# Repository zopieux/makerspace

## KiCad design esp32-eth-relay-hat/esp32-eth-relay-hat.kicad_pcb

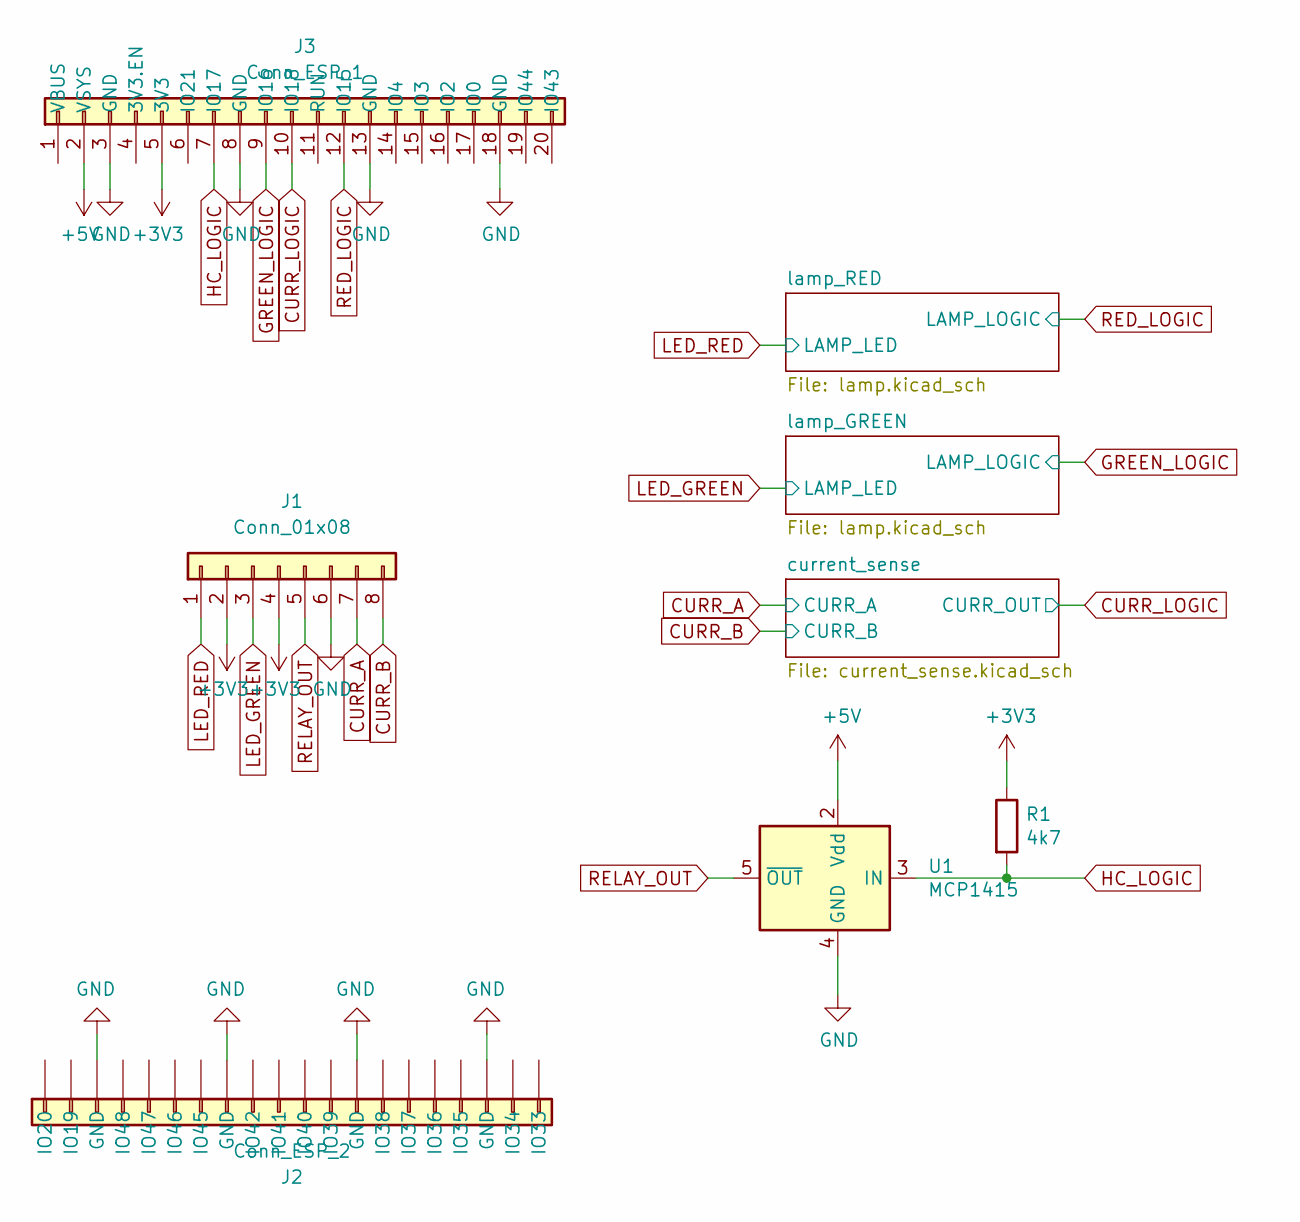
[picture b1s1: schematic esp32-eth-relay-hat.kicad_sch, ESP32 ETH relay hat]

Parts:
J1: Conn_01x08; TerminalBlock_Phoenix_MKDS-1,5-8_1x08_P5.00mm_Horizontal
J2: Conn_ESP_2; PinSocket_1x20_P2.54mm_Vertical
J3: Conn_ESP_1; PinSocket_1x20_P2.54mm_Vertical
R1: 4k7; R_0603_1608Metric_Pad0.98x0.95mm_HandSolder
U1: MCP1415; SOT-23-5

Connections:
+3V3: J1.2, J1.4, J3.5 (3V3), R1.1
+5V: J3.2 (VSYS), U1.2 (Vdd); also elsewhere on the board
CURR_A: J1.7; also elsewhere on the board
CURR_B: J1.8; also elsewhere on the board
CURR_LOGIC: J3.10 (IO18); also elsewhere on the board
GND: J1.6, J2.3 (GND), J2.8 (GND), J2.13 (GND), J2.18 (GND), J3.3 (GND), J3.8 (GND), J3.13 (GND), J3.18 (GND), U1.4 (GND); also elsewhere on the board
GREEN_LOGIC: J3.9 (IO16); also elsewhere on the board
HC_LOGIC: J3.7 (IO17), R1.2, U1.3 (IN)
LED_GREEN: J1.3; also elsewhere on the board
LED_RED: J1.1; also elsewhere on the board
RED_LOGIC: J3.12 (IO15); also elsewhere on the board
RELAY_OUT: J1.5, U1.5 (~OUT)

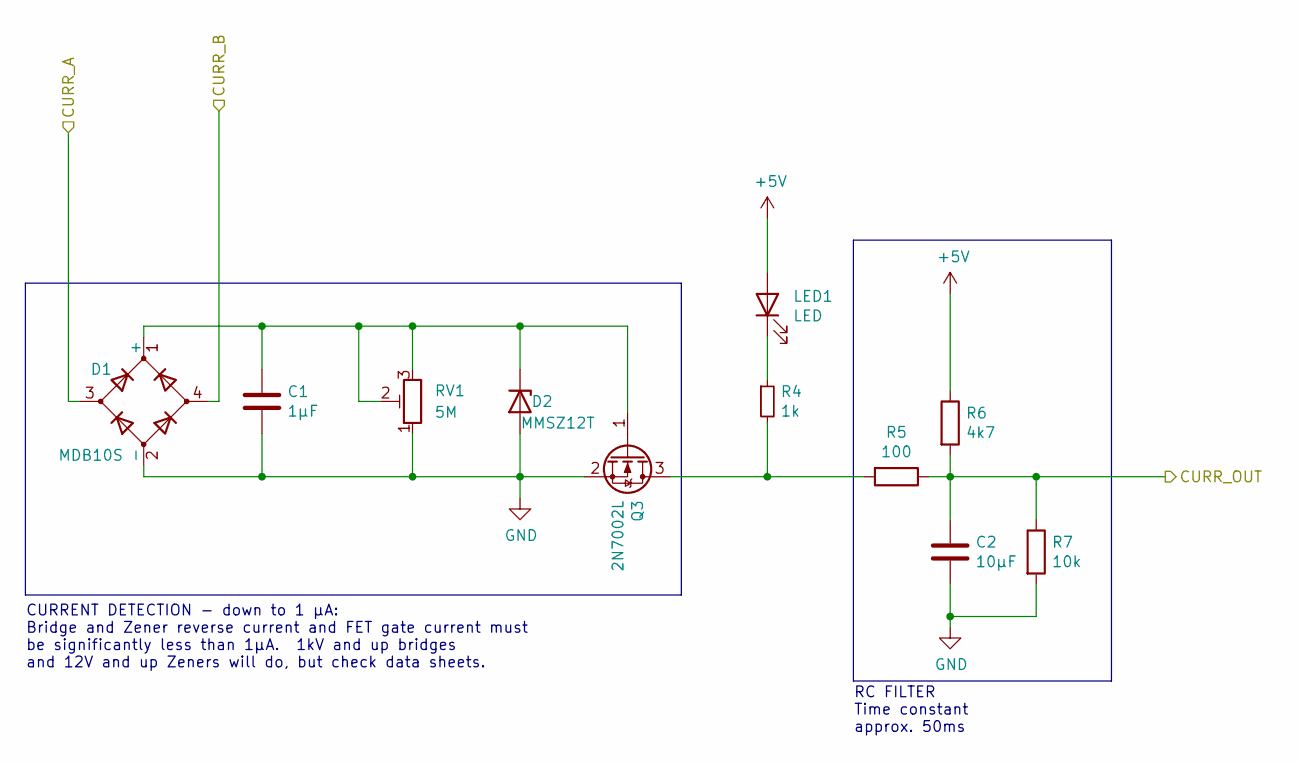
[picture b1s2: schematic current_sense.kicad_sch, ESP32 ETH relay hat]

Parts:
C1: 1µF; C_0603_1608Metric_Pad1.08x0.95mm_HandSolder
C2: 10µF; C_0603_1608Metric_Pad1.08x0.95mm_HandSolder
D1: MDB10S; Diode_Bridge_Diotec_ABS
D2: MMSZ12T; D_SOD-123
LED1: LED; LED_0603_1608Metric_Pad1.05x0.95mm_HandSolder
Q3: 2N7002L; SOT-23_Handsoldering
R4: 1k; R_0603_1608Metric_Pad0.98x0.95mm_HandSolder
R5: 100; R_0603_1608Metric_Pad0.98x0.95mm_HandSolder
R6: 4k7; R_0603_1608Metric_Pad0.98x0.95mm_HandSolder
R7: 10k; R_0603_1608Metric_Pad0.98x0.95mm_HandSolder
RV1: 5M; Potentiometer_Bourns_3386P_Vertical

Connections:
+5V: LED1.2 (A), R6.1; also elsewhere on the board
CURR_A: D1.3; also elsewhere on the board
CURR_B: D1.4; also elsewhere on the board
CURR_LOGIC: C2.1, R5.1, R6.2, R7.1; also elsewhere on the board
GND: C1.2, C2.2, D1.2 (-), D2.2 (A), Q3.2 (S), R7.2, RV1.1; also elsewhere on the board
unnamed: C1.1, D1.1 (+), D2.1 (K), Q3.1 (G), RV1.2, RV1.3
unnamed: LED1.1 (K), R4.1
unnamed: Q3.3 (D), R4.2, R5.2

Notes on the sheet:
RC FILTER Time constant approx. 50ms
CURRENT DETECTION - down to 1 µA: Bridge and Zener reverse current and FET gate current must be significantly less than 1µA. 1kV and up bridges and 12V and up Zeners will do, but check data sheets.

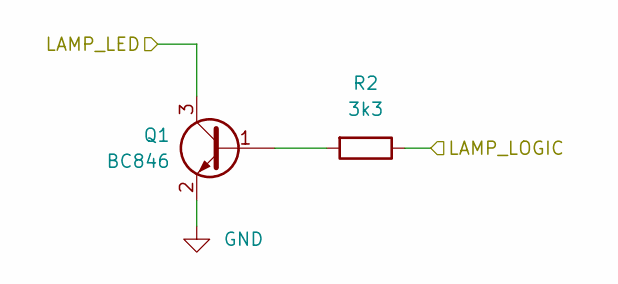
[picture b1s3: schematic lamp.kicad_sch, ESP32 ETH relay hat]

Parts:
Q1: BC846; SOT-23_Handsoldering
R2: 3k3; R_0603_1608Metric_Pad0.98x0.95mm_HandSolder

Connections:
GND: Q1.2 (E); also elsewhere on the board
LED_RED: Q1.3 (C); also elsewhere on the board
unnamed: Q1.1 (B), R2.2
RED_LOGIC: R2.1; also elsewhere on the board

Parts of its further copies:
Q2: BC846; SOT-23_Handsoldering
R3: 3k3; R_0603_1608Metric_Pad0.98x0.95mm_HandSolder

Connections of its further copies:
GND: Q2.2 (E); also elsewhere on the board
GREEN_LOGIC: R3.1; also elsewhere on the board
LED_GREEN: Q2.3 (C); also elsewhere on the board
unnamed: Q2.1 (B), R3.2

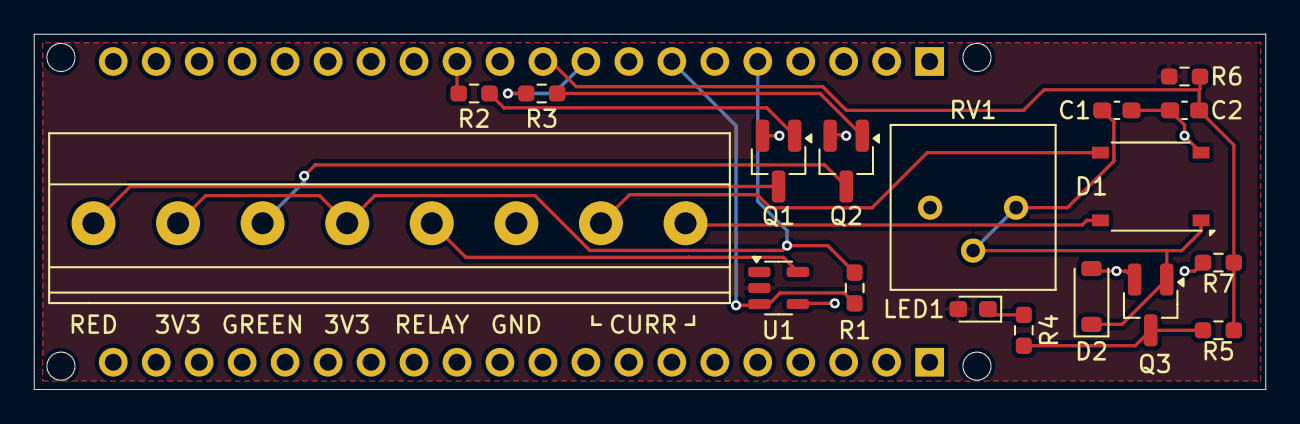
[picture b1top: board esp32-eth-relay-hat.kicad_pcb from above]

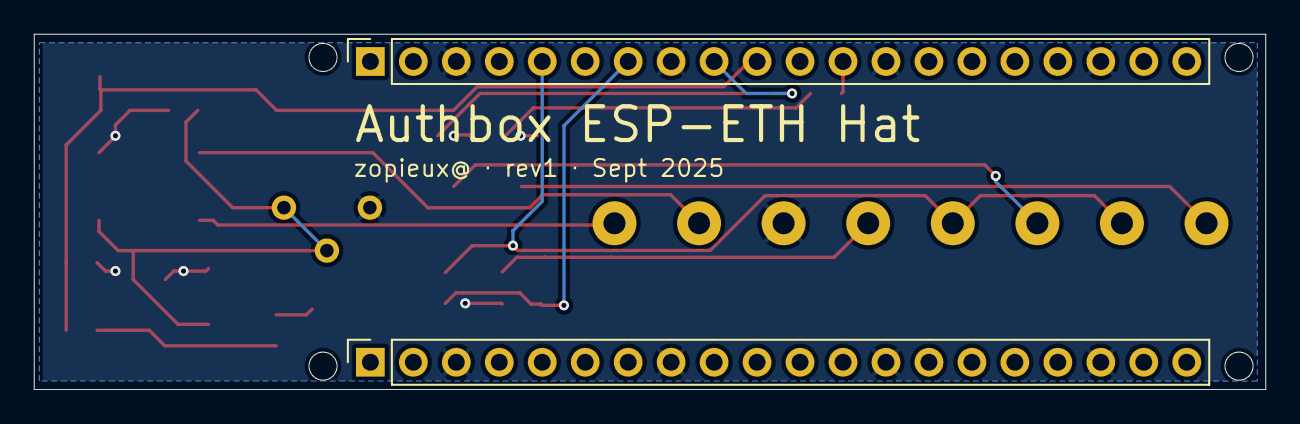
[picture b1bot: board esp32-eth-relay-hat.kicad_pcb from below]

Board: 2 copper layers, 72.8 x 21.0 mm, 24 parts (2 on the bottom side), 17 nets.

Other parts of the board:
MNT1, MNT2, MNT3, MNT4: 1.66mm; MountingHole_1.66mm

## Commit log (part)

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2024-09-22 Initial commit.
2024-10-20 Add gauthbox draft.
2024-10-20 Only build when requested.
2024-10-22 Add buttonless.
2024-10-22 Add sdcard mount for local config.
2024-10-23 Update gitignore.
2024-10-23 Add and enable gauthbox package.
2024-10-23 More build instructions.
2024-10-23 Enable vfat fs support as it's necessary for reading the sdcard.
2024-10-23 Fix flake. Sadly this is not working as intended because of the sandbox.
2024-10-23 Add go vendoring to the workflow.
    ci: build
2024-10-23 Add sdcard.mount and update authbox.service.
2024-10-23 gauthbox: Reach a working, reliable state for buttonless.
2024-10-23 Disable blink-led-error.
2024-10-23 Make leds subsystem writable by group "input".
    ci: build
2024-10-23 Repurpose fake Python server to also serve the config.
2024-10-23 Add a test mosquitto server script.
2024-10-23 Fix DEVELOP instructions.
2024-10-23 Fix sdcard label. Add missing URL to authbox.service.
    ci: build
2024-10-24 Add missing include in main Config.in.
2024-10-24 Use control.woodshop-zrh for control/command and logs.
    ci: build
2024-10-26 Attempt to cache host & toolchain build artifacts.
    ci: build
2024-10-26 Generate a directory in addition to 7z.
2024-10-26 Improve README instructions and context.
2024-10-26 Add workflow_dispatch trigger.
2024-10-26 More deterministic cache hash, hopefully.
    Crimes against humanity are included.
    ci: build
2024-10-26 Don't subshell.
2024-10-26 Minor cleanups and add documentation.
    ci: build
2024-10-26 Add size estimates.
2024-10-26 Add release from action.
    ci: build
2024-10-26 More robust 7z make.
    Create draft releases as part of the workflow.
2024-10-31 Add dependency on systemd-hostnamed.service.
    ci: build
2024-10-31 Do not rely on LoadCredential, the unit fails if not available.
2024-10-31 Fix Go warnings.
2024-10-31 Add activeLow config and handling.
    ci: build
2025-01-16 Rework gauthbox MQTT logic.
    ci: build
2025-01-16 Fix fake testing values.
2025-01-16 Fix relay and badge component platform.
    ci: build
2025-01-16 Add availability status with Last Will Testament.
    ci: build
2025-01-16 Add gitignore.
2025-01-16 Add authbox_config cmd to serve templated configs.
2025-01-19 Add an sftp server so we can 'scp'.
2025-01-19 Add a post-build.sh script with some cleanups.
2025-01-19 Update MOTD.
2025-01-19 Add minor things to sysctl.
2025-01-19 Enable systemd-journal-upload.
    Motherfucking presets got me confused real good.
2025-01-19 Reduce journald size, disable coredump.
2025-01-19 Switch to special ssh key.
    ci: build
2025-01-30 Make LWT and online messages retained.
    ci: build
2025-01-30 Allow config customization per authbox.
    The setByPath code is LLM generated, I cannot be bothered.
2025-02-08 Add ability to self-reset upon receiving a request on some mqtt topic.
2025-02-08 Do not succeed on config HTTP error.
2025-02-08 Add README.
2025-03-06 Use a simple boolean for badged-in.
2025-03-06 Implement "access allowed" feature.
2025-05-06 Add state_class 'measurement' for long-term (>10d) aggregated retention.
2025-07-03 Don't use 'measurement' for booleans, this is not compatible.
    ci: build
2025-09-17 Add esp32-eth-relay-hat PCB design.
2026-03-11 wifi-usb: minimal alpine USB gadget
2026-05-09 More wifi-usb for HA.
2026-05-11 wifi-usb: USB mode switching, detach on rm 'LOG OUT', etc.
2026-05-12 Fix FAT32 layout.
2026-05-12 Fix extension filtering.
2026-05-26 Add CONFIG_URL. Add USB selection through GPIO. Minor fixes.
2026-05-28 gauthbox: refactor to add CNC stuff, add tests, use jsonnet config.
2026-05-28 wifi-usb: use root flake, remove gadget-web, use gauthbox primitives.
2026-05-30 Bump buildroot branch so that Go is less ancient. Cleanup flakes.
    ci: build
2026-06-09 gitignore
2026-06-09 Add logout & reload gpio inputs.
